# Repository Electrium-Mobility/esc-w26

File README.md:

# Electrium Mobility 2026 ESC
This repository contains all the firmware and hardware for Electrium Mobility's 2026 ESC, which is a 36V/15A 3-phase BLDC motor controller built around the STSPIN32G4 SiP's integrated gate driver and STM32G4 MCU, supporting 6-step and FOC commutation!

## Architecture

## Features

### Power
- **Voltage**: 10-36V (maximum 10S battery pack)
- **Current**: 15A continuous (25A peak)
- **Power**: 500W (implied by above)
- External 5V/1A Buck Regulator
- Internal VCC (using 10V)/200mA Buck Regulator
- Internal 3.3V/150mA LDO
- 1410uF Bulk Capacitor Bank (bleed resistor discharges it in 1 min)

### Input Protection
- Reverse Polarity Protection (dual back-to-back PMOS)
- Inrush Current Limiting (RC soft-start)
- Transient Overvoltage Protection (60V TVS clamp)
- Short-circuit and Overcurrent Protection (SCREF divider)

### Sensing
- Phase Currents (0.5m shunt resistors) using Internal PGA with Overcurrent Protection (note: measures negative currents, but regenerative braking is not supported)
- Phase Voltages (for sensorless feedback method using BEMF zero-crossings)
- PCB Temperature (NTC thermistor)

### Interfaces
- Power Supply Input (VM+, VM-)
- SWD Programming/Debug (STDC14)
- **Throttle**: UART (digital commands), ADC (analog pot)
- **Motor**: Phase Outputs (U, V, W), Hall Sensors (A, B, C), Winding Temperature
- CAN (FD)
- Expansion Headers: SPI, I2C, 4 unused pins

### User I/O
- **Buttons**: RESET, BOOT, USER
- **LEDs**: Power Rails, READY, FAULT, 2 configurable (STATUS1, STATUS2)
- Onboard Test Points

### Board 
- 4-layer (stackup: Signal/Power, Ground, Ground, Signal)
- 125x80mm with 2oz Outer and 0.5oz Inner Copper
- Partitioned Grounding Scheme (separates high-power PGND and logic GND)

## Schematic

## Routing

### Coloured (Traces Only, With Zones and Silkscreen)

### Colourless (Traces Only, With Zones and Silkscreen)

## 3D Renders

## Assembled Board
⚠️Under Construction⚠️

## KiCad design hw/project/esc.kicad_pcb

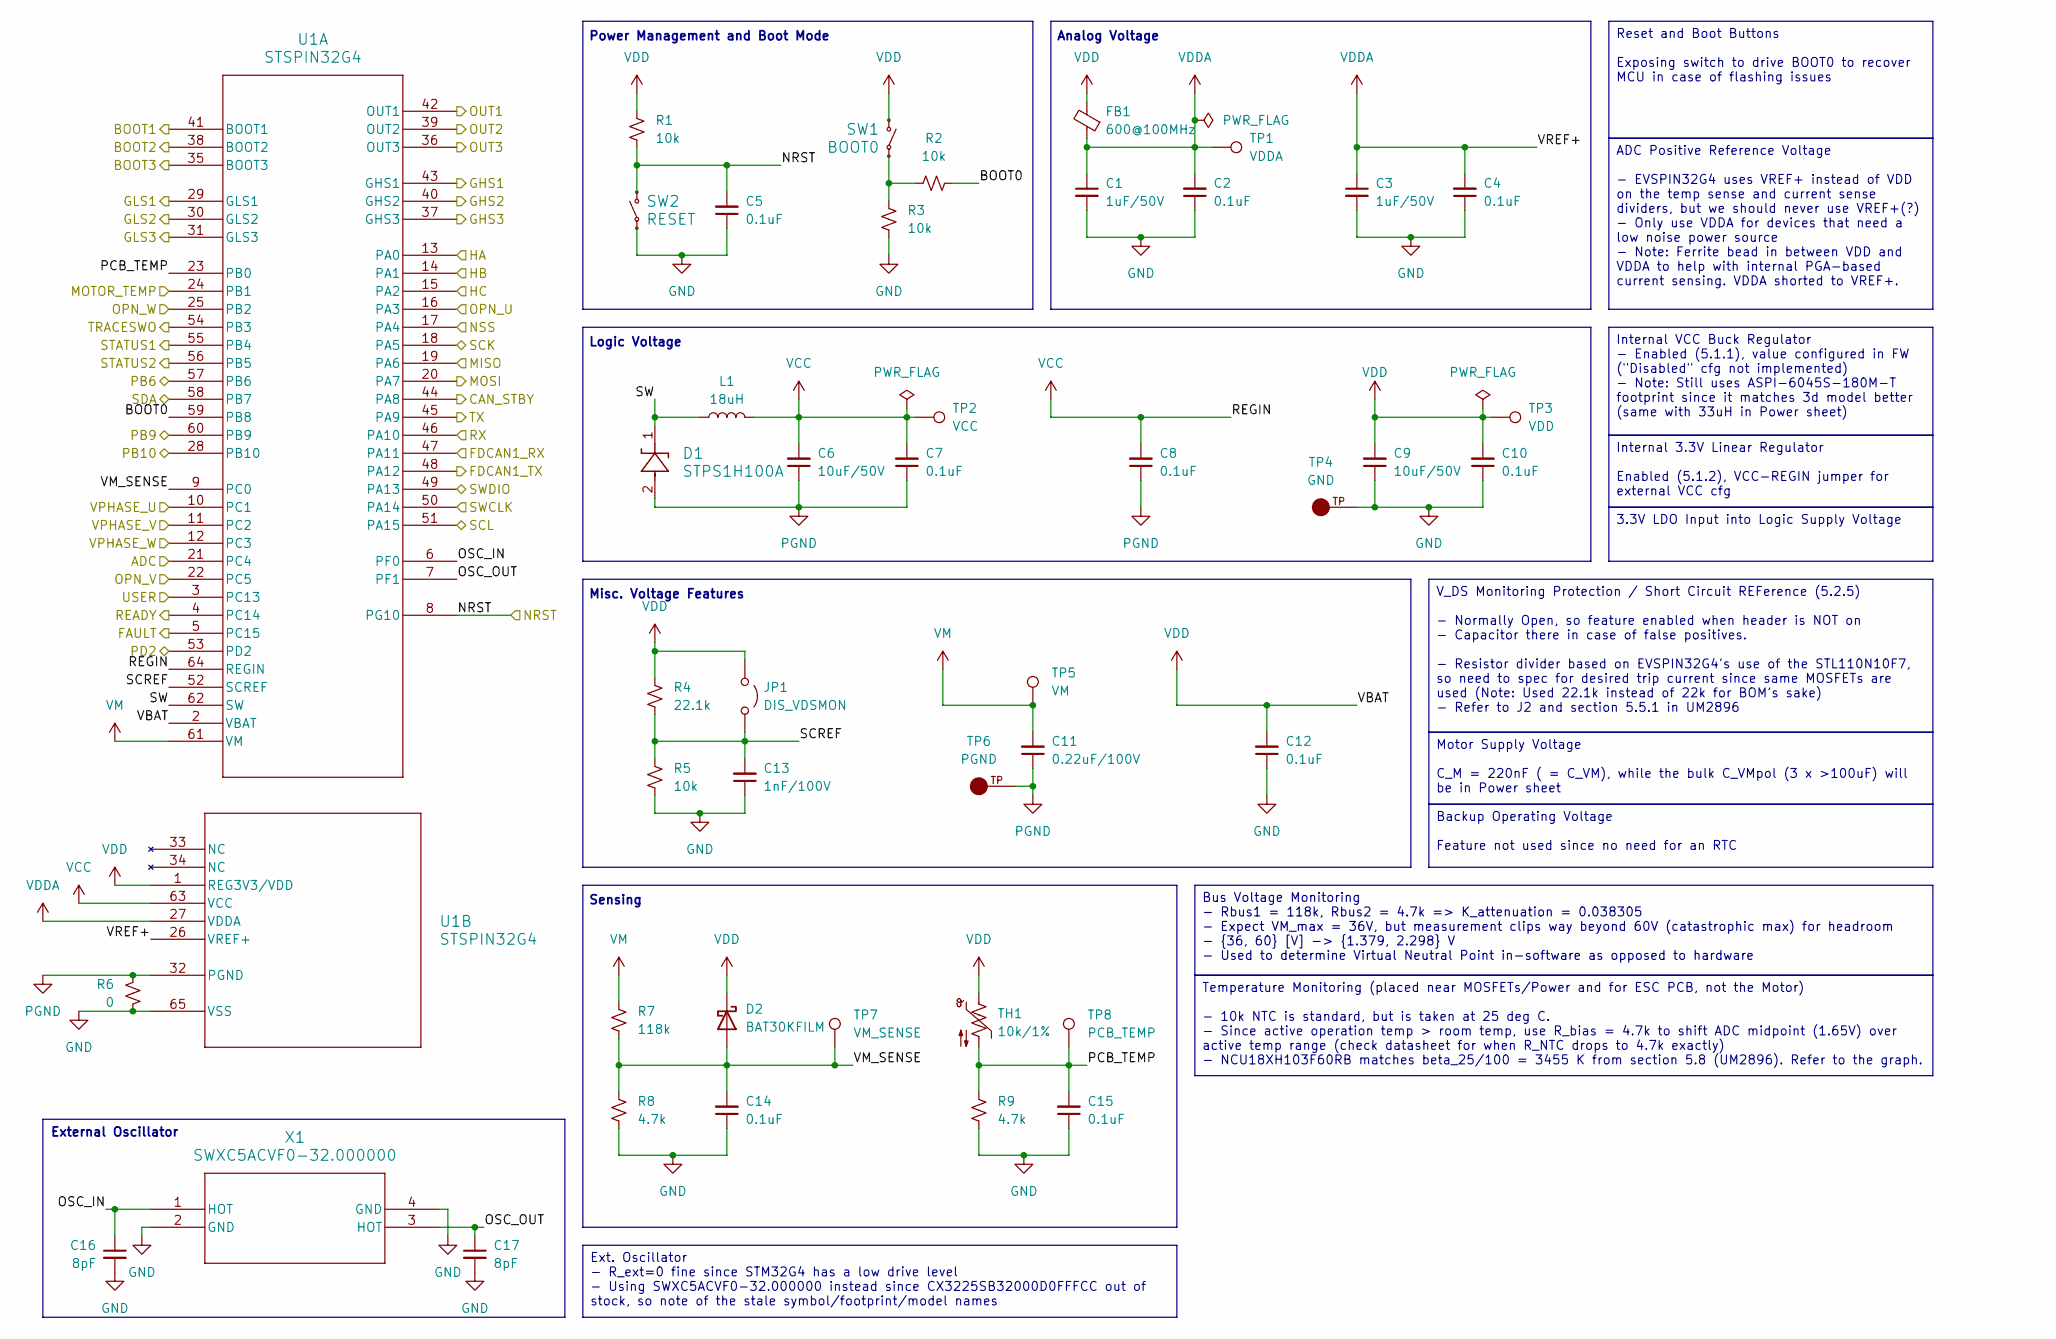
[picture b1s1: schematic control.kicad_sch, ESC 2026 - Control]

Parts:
C1, C3: 1uF/50V; C_0603_1608Metric; LCSC C15849
C2, C4, C5, C7, C8, C10, C12, C14, C15: 0.1uF; C_0603_1608Metric; LCSC C15725
C6, C9: 10uF/50V; C_0805_2012Metric; LCSC C440198
C11: 0.22uF/100V; C_0603_1608Metric; LCSC C2169715
C13: 1nF/100V; C_0603_1608Metric; LCSC C113793
C16, C17: 8pF; C_0603_1608Metric; LCSC C519117
D1: STPS1H100A; SMA_STM; LCSC C165701
D2: BAT30KFILM; D_SOD-523; LCSC C2926449
FB1: 600@100MHz; L_0603_1608Metric; LCSC C304319
JP1: DIS_VDSMON; PinHeader_1x02_P2.54mm_Vertical; LCSC C5426960
L1: 18uH; L_Sunlord_SWPA6045S; LCSC C96954
R1, R2, R3, R5: 10k; R_0603_1608Metric; LCSC C25804
R4: 22.1k; R_0603_1608Metric; LCSC C25961
R6: 0; R_0603_1608Metric; LCSC C21189
R7: 118k; R_0603_1608Metric; LCSC C25806
R8, R9: 4.7k; R_0603_1608Metric; LCSC C23162
SW1: BOOT0; TS-1187A-B-A-B; LCSC C318884
SW2: RESET; TS-1187A-B-A-B; LCSC C318884
TH1: 10k/1%; R_0603_1608Metric; LCSC C440252
TP1: VDDA; TestPoint_Pad_D1.0mm_with_More_Clearance
TP2: VCC; TestPoint_Pad_D1.0mm_with_More_Clearance
TP3: VDD; TestPoint_Pad_D1.0mm_with_More_Clearance
TP4: GND; KEYSTONE_5016; PARTREV D; DigiKey_Part_Number 36-5016CT-ND
TP5: VM; TestPoint_Pad_D1.0mm_with_More_Clearance
TP6: PGND; KEYSTONE_5016; PARTREV D; DigiKey_Part_Number 36-5016CT-ND
TP7: VM_SENSE; TestPoint_Pad_D1.0mm_with_More_Clearance
TP8: PCB_TEMP; TestPoint_Pad_D1.0mm_with_More_Clearance
U1: STSPIN32G4; QFN_IN32G4_STM; LCSC C7434864
X1: SWXC5ACVF0-32.000000; xtal4_CX3225SB_AVX; LCSC C22399832

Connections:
/Control/ADC: U1.21 (PC4); also elsewhere on the board
/Control/BOOT0: R2.2, U1.59 (PB8)
/Control/BOOT1: U1.41 (BOOT1); also elsewhere on the board
/Control/BOOT2: U1.38 (BOOT2); also elsewhere on the board
/Control/BOOT3: U1.35 (BOOT3); also elsewhere on the board
/Control/CAN_STBY: U1.44 (PA8); also elsewhere on the board
/Control/FAULT: U1.5 (PC15); also elsewhere on the board
/Control/FDCAN1_RX: U1.47 (PA11); also elsewhere on the board
/Control/FDCAN1_TX: U1.48 (PA12); also elsewhere on the board
/Control/GHS1: U1.43 (GHS1); also elsewhere on the board
/Control/GHS2: U1.40 (GHS2); also elsewhere on the board
/Control/GHS3: U1.37 (GHS3); also elsewhere on the board
/Control/GLS1: U1.29 (GLS1); also elsewhere on the board
/Control/GLS2: U1.30 (GLS2); also elsewhere on the board
/Control/GLS3: U1.31 (GLS3); also elsewhere on the board
/Control/HA: U1.13 (PA0); also elsewhere on the board
/Control/HB: U1.14 (PA1); also elsewhere on the board
/Control/HC: U1.15 (PA2); also elsewhere on the board
/Control/MISO: U1.19 (PA6); also elsewhere on the board
/Control/MOSI: U1.20 (PA7); also elsewhere on the board
/Control/MOTOR_TEMP: U1.24 (PB1); also elsewhere on the board
/Control/NRST: C5.2, R1.2, SW2.1, SW2.2, U1.8 (PG10); also elsewhere on the board
/Control/NSS: U1.17 (PA4); also elsewhere on the board
/Control/OPN_U: U1.16 (PA3); also elsewhere on the board
/Control/OPN_V: U1.22 (PC5); also elsewhere on the board
/Control/OPN_W: U1.25 (PB2); also elsewhere on the board
/Control/OSC_IN: C16.1, U1.6 (PF0), X1.1 (HOT)
/Control/OSC_OUT: C17.1, U1.7 (PF1), X1.3 (HOT)
/Control/PB6: U1.57 (PB6); also elsewhere on the board
/Control/PB9: U1.60 (PB9); also elsewhere on the board
/Control/PB10: U1.28 (PB10); also elsewhere on the board
/Control/PCB_TEMP: C15.2, R9.1, TH1.2, TP8.1 (1_1), U1.23 (PB0)
/Control/PD2: U1.53 (PD2); also elsewhere on the board
/Control/READY: U1.4 (PC14); also elsewhere on the board
/Control/RX: U1.46 (PA10); also elsewhere on the board
/Control/SCK: U1.18 (PA5); also elsewhere on the board
/Control/SCL: U1.51 (PA15); also elsewhere on the board
/Control/SCREF: C13.2, JP1.2 (B), R4.2, R5.1, U1.52 (SCREF)
/Control/SDA: U1.58 (PB7); also elsewhere on the board
/Control/STATUS1: U1.55 (PB4); also elsewhere on the board
/Control/STATUS2: U1.56 (PB5); also elsewhere on the board
/Control/SW: D1.1, L1.1, U1.62 (SW)
/Control/SWCLK: U1.50 (PA14); also elsewhere on the board
/Control/SWDIO: U1.49 (PA13); also elsewhere on the board
/Control/TRACESWO: U1.54 (PB3); also elsewhere on the board
/Control/TX: U1.45 (PA9); also elsewhere on the board
/Control/USER: U1.3 (PC13); also elsewhere on the board
/Control/VM_SENSE: C14.2, D2.2 (A), R7.2, R8.1, TP7.1 (1_1), U1.9 (PC0)
/Control/VPHASE_U: U1.10 (PC1); also elsewhere on the board
/Control/VPHASE_V: U1.11 (PC2); also elsewhere on the board
/Control/VPHASE_W: U1.12 (PC3); also elsewhere on the board
/Drive/U: U1.42 (OUT1); also elsewhere on the board
/Drive/V: U1.39 (OUT2); also elsewhere on the board
/Drive/W: U1.36 (OUT3); also elsewhere on the board
GND: C1.2, C2.1, C3.2, C4.1, C5.1, C9.1, C10.1, C12.1, C13.1, C14.1, C15.1, C16.2, C17.2, R3.2, R5.2, R6.1, R8.2, R9.2, SW2.3, SW2.4, TP4.TP, U1.65 (VSS), X1.2 (GND), X1.4 (GND); also elsewhere on the board
unnamed: R2.1, R3.1, SW1.3, SW1.4
PGND: C6.1, C7.1, C8.1, C11.1, D1.2, R6.2, TP6.TP, U1.32 (PGND); also elsewhere on the board
VCC: C6.2, C7.2, C8.2, L1.2, TP2.1 (1_1), U1.63 (VCC), U1.64 (REGIN); also elsewhere on the board
VDD: C9.2, C10.2, C12.2, D2.1 (K), FB1.2, JP1.1 (A), R1.1, R4.1, SW1.1, SW1.2, TH1.1, TP3.1 (1_1), U1.1 (REG3V3/VDD), U1.2 (VBAT); also elsewhere on the board
VDDA: C1.1, C2.2, C3.1, C4.2, FB1.1, TP1.1 (1_1), U1.26 (VREF+), U1.27 (VDDA)
VM: C11.2, R7.1, TP5.1 (1_1), U1.61 (VM); also elsewhere on the board

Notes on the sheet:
Analog Voltage
Misc. Voltage Features
Logic Voltage
Sensing
Power Management and Boot Mode
External Oscillator
Backup Operating Voltage Feature not used since no need for an RTC
3.3V LDO Input into Logic Supply Voltage
V_DS Monitoring Protection / Short Circuit REFerence (5.2.5) - Normally Open, so feature enabled when header is NOT on - Capacitor there in case of false positives. - Resistor divider based on EVSPIN32G4's use of the STL110N10F7, so need to spec for desired trip current since same MOSFETs are used 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
Internal 3.3V Linear Regulator Enabled (5.1.2), VCC-REGIN jumper for external VCC cfg
Internal VCC Buck Regulator - Enabled (5.1.1), value configured in FW ("Disabled" cfg not implemented) - Note: Still uses ASPI-6045S-180M-T footprint since it matches 3d model better (same with 33uH in Power sheet)
Temperature Monitoring (placed near MOSFETs/Power and for ESC PCB, not the Motor) - 10k NTC is standard, but is taken at 25 deg C. - Since active operation temp > room temp, use R_bias = 4.7k to shift ADC midpoint (1.65V) over active temp range (check datasheet for when R_NTC drops to 4.7k exactly)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
ADC Positive Reference Voltage - EVSPIN32G4 uses VREF+ instead of VDD on the temp sense and current sense dividers, but we should never use VREF+(?) - Only use VDDA for devices that need a low noise power source - Note: Ferrite bead in between VDD and VDDA to help with internal PGA-based current se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
Ext. Oscillator - R_ext=0 fine since STM32G4 has a low drive level - Using SWXC5ACVF0-32.000000 instead since CX3225SB32000D0FFFCC out of stock, so note of the stale symbol/footprint/model names
Motor Supply Voltage C_M = 220nF ( = C_VM), while the bulk C_VMpol (3 x >100uF) will be in Power sheet
Reset and Boot Buttons Exposing switch to drive BOOT0 to recover MCU in case of flashing issues
Bus Voltage Monitoring - Rbus1 = 118k, Rbus2 = 4.7k => K_attenuation = 0.038305 - Expect VM_max = 36V, but measurement clips way beyond 60V (catastrophic max) for headroom - {36, 60} [V] -> {1.379, 2.298} V - Used to determine Virtual Neutral Point in-software as opposed to hardware

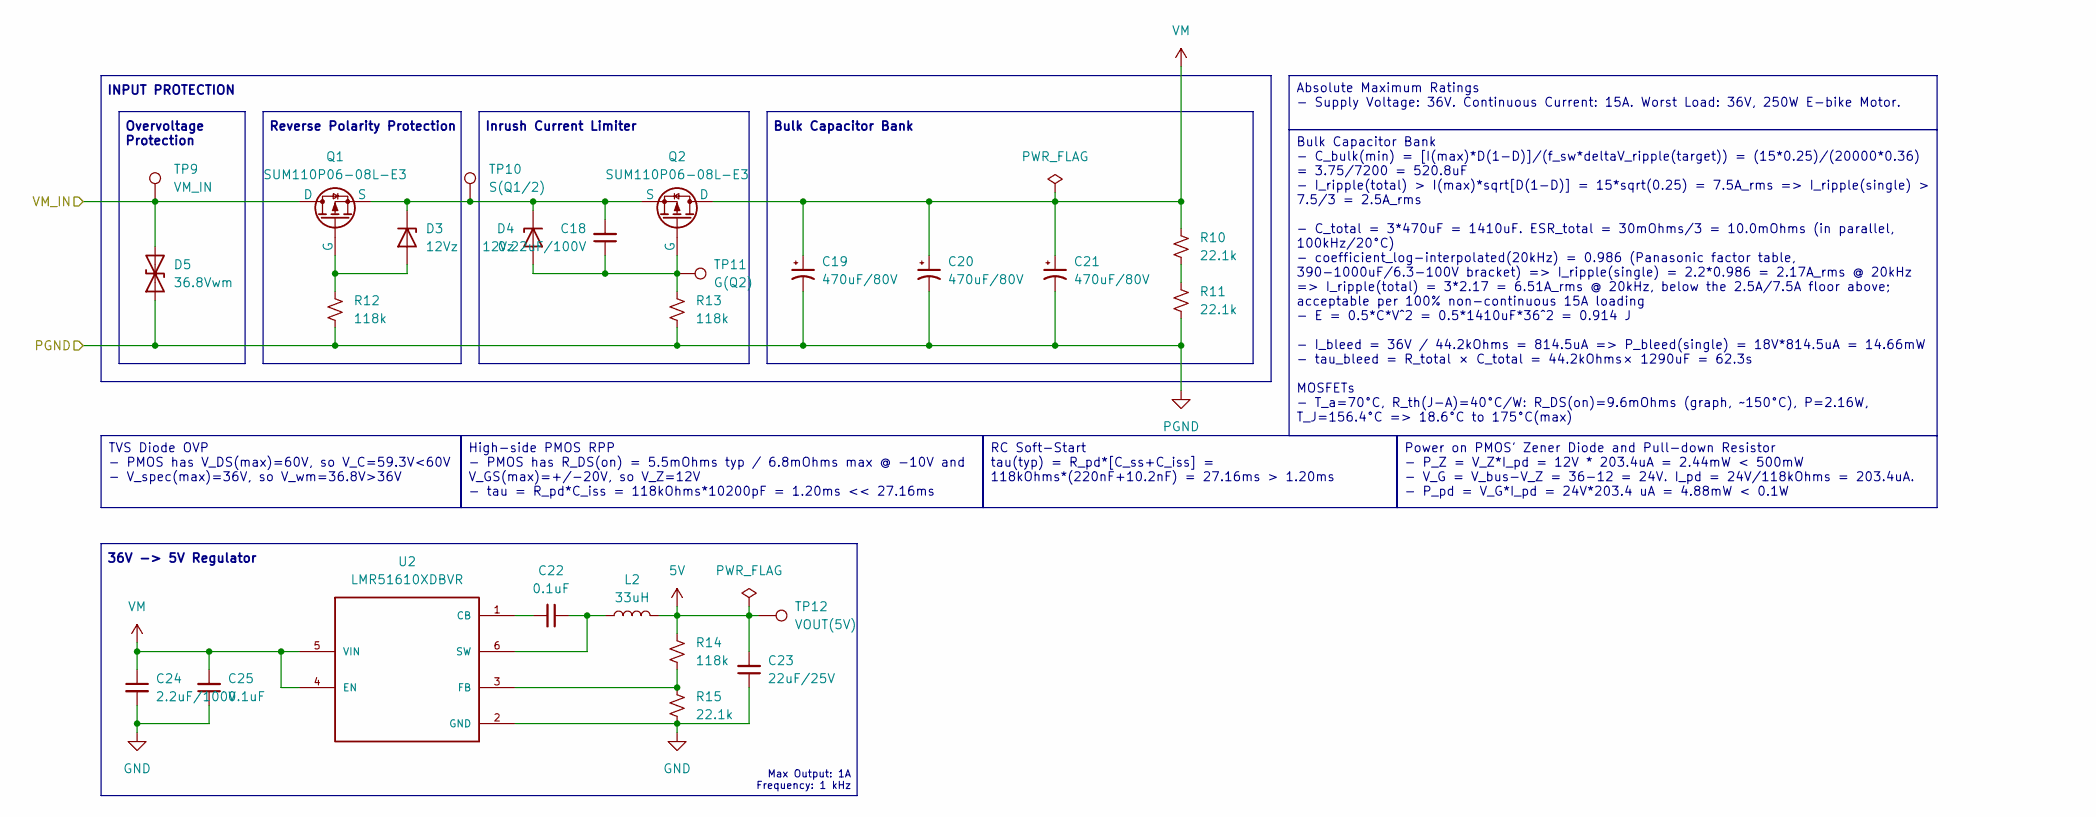
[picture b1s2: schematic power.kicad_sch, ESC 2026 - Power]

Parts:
C18: 0.22uF/100V; C_0603_1608Metric; LCSC C2169715
C19, C20, C21: 470uF/80V; CP_Radial_D12.5mm_P5.00mm; LCSC C385881
C22, C25: 0.1uF; C_0603_1608Metric; LCSC C15725
C23: 22uF/25V; C_0805_2012Metric; LCSC C45783
C24: 2.2uF/100V; C_0805_2012Metric; LCSC C2981733
D3, D4: 12Vz; D_SOD-123; LCSC C699126
D5: 36.8Vwm; D_SMB; LCSC C468909
L2: 33uH; L_Sunlord_SWPA6045S; LCSC C83451
Q1, Q2: SUM110P06-08L-E3; TO-263-2; LCSC C5364638
R10, R11, R15: 22.1k; R_0603_1608Metric; LCSC C25961
R12, R13, R14: 118k; R_0603_1608Metric; LCSC C25806
TP9: VM_IN; TestPoint_Pad_D1.0mm_with_More_Clearance
TP10: S(Q1/2); TestPoint_Pad_D1.0mm_with_More_Clearance
TP11: G(Q2); TestPoint_Pad_D1.0mm_with_More_Clearance
TP12: VOUT(5V); TestPoint_Pad_D1.0mm_with_More_Clearance
U2: LMR51610XDBVR; LMR51610XDBVR-SOT95P280X145-6N; PARTREV B; LCSC C20539658

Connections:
5V: C23.2, L2.2, R14.1, TP12.1 (1_1); also elsewhere on the board
/Peripherals/VM_IN: D5.2 (A2), Q1.2 (D), TP9.1 (1_1); also elsewhere on the board
GND: C23.1, C24.2, C25.1, R15.2, U2.2 (GND); also elsewhere on the board
unnamed: D3.2 (A), Q1.1 (G), R12.1
unnamed: C18.2, D3.1 (K), D4.1 (K), Q1.3 (S), Q2.3 (S), TP10.1 (1_1)
unnamed: C18.1, D4.2 (A), Q2.1 (G), R13.1, TP11.1 (1_1)
unnamed: R10.2, R11.1
unnamed: C22.2, U2.1 (CB)
unnamed: R14.2, R15.1, U2.3 (FB)
unnamed: C22.1, L2.1, U2.6 (SW)
PGND: C19.2, C20.2, C21.2, D5.1 (A1), R11.2, R12.2, R13.2; also elsewhere on the board
VM: C19.1, C20.1, C21.1, C24.1, C25.2, Q2.2 (D), R10.1, U2.4 (EN), U2.5 (VIN); also elsewhere on the board

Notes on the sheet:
Overvoltage Protection
Max Output: 1A Frequency: 1 kHz
36V -> 5V Regulator
INPUT PROTECTION
Inrush Current Limiter
Bulk Capacitor Bank
Reverse Polarity Protection
RC Soft-Start tau(typ) = R_pd*[C_ss+C_iss] = 118kOhms*(220nF+10.2nF) = 27.16ms > 1.20ms
TVS Diode OVP - PMOS has V_DS(max)=60V, so V_C=59.3V<60V - V_spec(max)=36V, so V_wm=36.8V>36V
High-side PMOS RPP - PMOS has R_DS(on) = 5.5mOhms typ / 6.8mOhms max @ -10V and V_GS(max)=+/-20V, so V_Z=12V - tau = R_pd*C_iss = 118kOhms*10200pF = 1.20ms << 27.16ms
Power on PMOS' Zener Diode and Pull-down Resistor - P_Z = V_Z*I_pd = 12V * 203.4uA = 2.44mW < 500mW - V_G = V_bus−V_Z = 36−12 = 24V. I_pd = 24V/118kOhms = 203.4uA. - P_pd = V_G*I_pd = 24V*203.4 uA = 4.88mW < 0.1W
Absolute Maximum Ratings - Supply Voltage: 36V. Continuous Current: 15A. Worst Load: 36V, 250W E-bike Motor.
Bulk Capacitor Bank - C_bulk(min) = [I(max)*D(1−D)]/(f_sw*deltaV_ripple(target)) = (15*0.25)/(20000*0.36) = 3.75/7200 = 520.8uF - I_ripple(total) > I(max)*sqrt[D(1−D)] = 15*sqrt(0.25) = 7.5A_rms => I_ripple(single) > 7.5/3 = 2.5A_rms - C_total = 3*470uF = 1410uF. ESR_total = 30mOhms/3 = 10.0mOhms (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

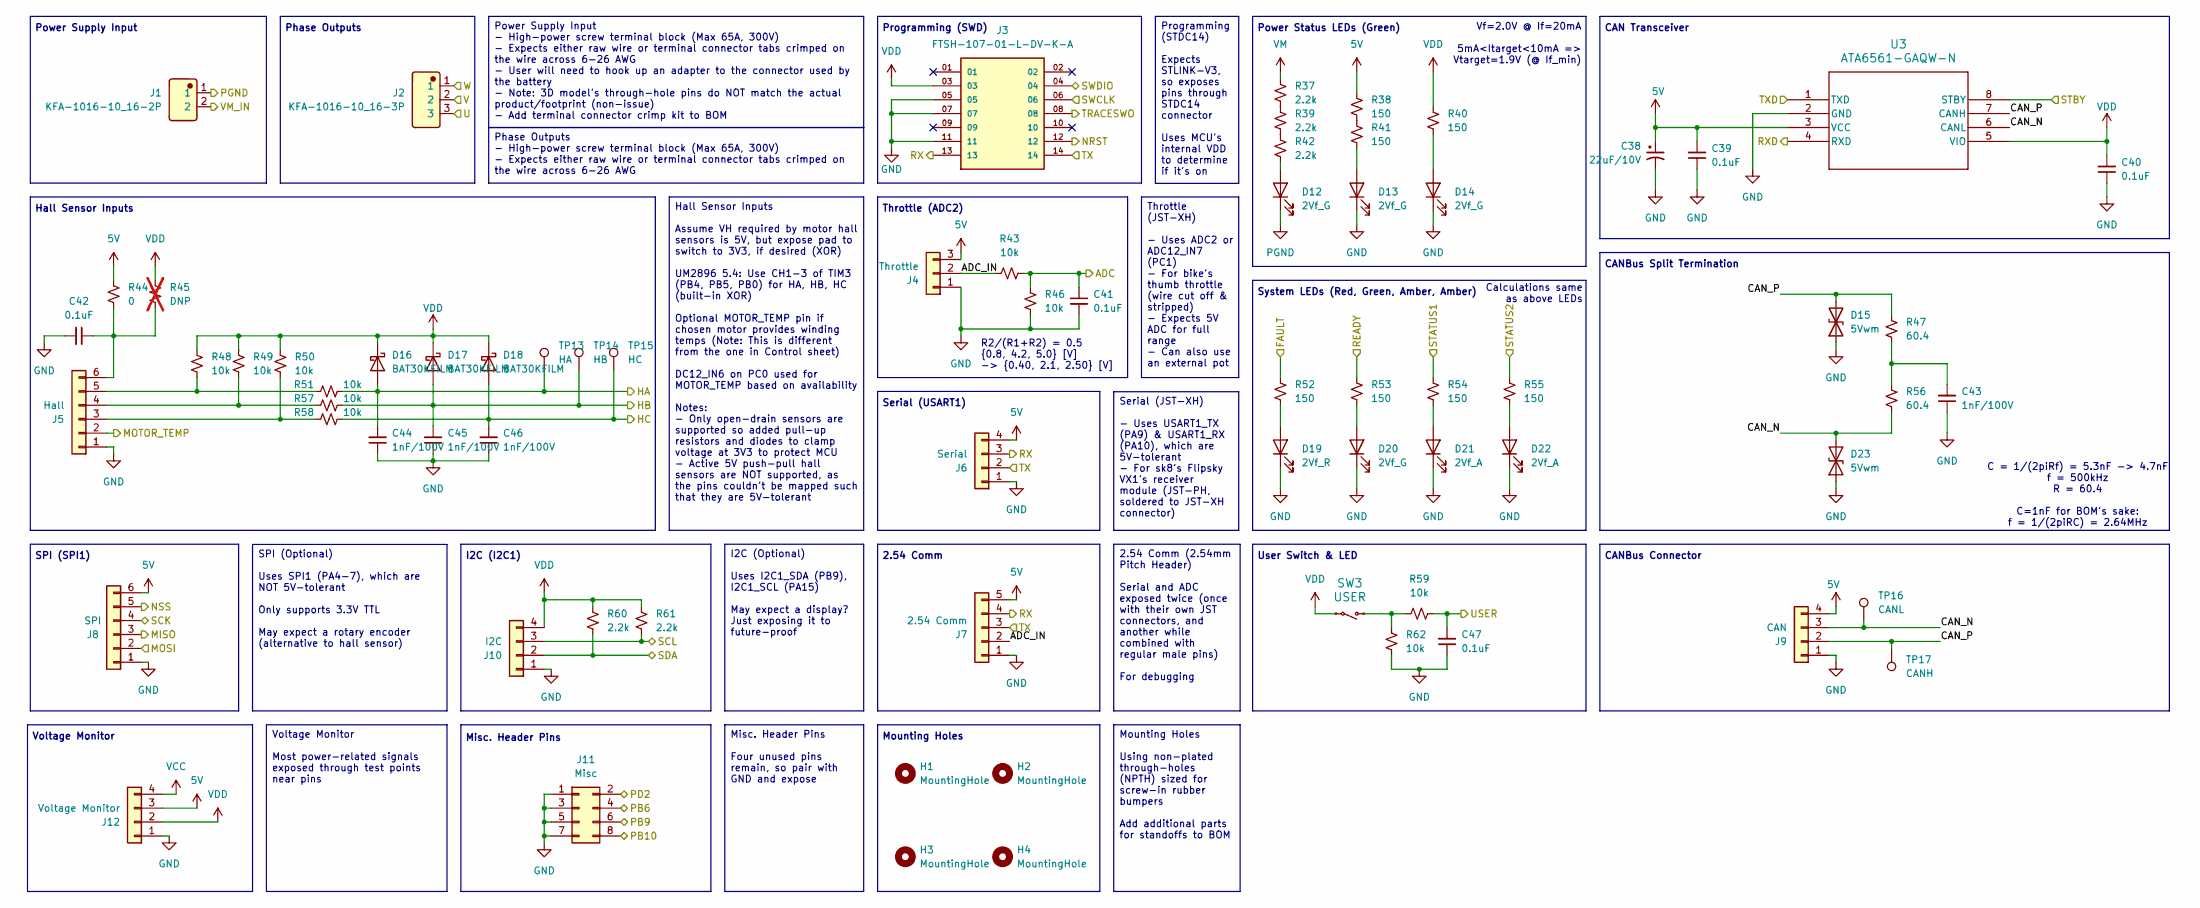
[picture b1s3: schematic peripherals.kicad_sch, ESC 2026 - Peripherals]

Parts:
C38: 22uF/10V; EEEFKC220UAR; LCSC C401733
C39, C40, C41, C42, C47: 0.1uF; C_0603_1608Metric; LCSC C15725
C43, C44, C45, C46: 1nF/100V; C_0603_1608Metric; LCSC C113793
D12, D13, D14, D20: 2Vf_G; LED_0603_1608Metric; LCSC C125098
D15, D23: 5Vwm; D_SOD-523; LCSC C51912417
D16, D17, D18: BAT30KFILM; D_SOD-523; LCSC C2926449
D19: 2Vf_R; LED_0603_1608Metric; LCSC C94869
D21, D22: 2Vf_A; LED_0603_1608Metric; LCSC C5730905
H1, H2, H3, H4: MountingHole; MountingHole_3.2mm_M3
J1: KFA-1016-10_16-2P; Manufacturer Part KFA-1016-10.16-2P; LCSC C475110
J2: KFA-1016-10_16-3P; Manufacturer Part KFA-1016-10.16-3P; LCSC C475111
J3: FTSH-107-01-L-DV-K-A; SAMTEC_FTSH-107-01-L-DV-K-A; PARTREV H; DigiKey_Part_Number FTSH-107-01-L-DV-K-A-ND
J4: Throttle; JST_XH_B3B-XH-A_1x03_P2.50mm_Vertical; LCSC C144394
J5: Hall; JST_XH_B6B-XH-A_1x06_P2.50mm_Vertical; LCSC C144397
J6: Serial; JST_XH_B4B-XH-A_1x04_P2.50mm_Vertical; LCSC C144395
J7: 2.54 Comm; PinHeader_1x05_P2.54mm_Vertical; LCSC C3347212
J8: SPI; PinHeader_1x06_P2.54mm_Vertical; LCSC C5427040
J9: CAN; JST_XH_B4B-XH-A_1x04_P2.50mm_Vertical; LCSC C144395
J10: I2C; PinHeader_1x04_P2.54mm_Vertical; LCSC C3329732
J11: Misc; PinHeader_2x04_P2.54mm_Vertical; LCSC C3333874
J12: Voltage Monitor; PinHeader_1x04_P2.54mm_Vertical; LCSC C3329732
R37, R39, R42, R60, R61: 2.2k; R_0603_1608Metric; LCSC C4190
R38, R40, R41, R52, R53, R54, R55: 150; R_0603_1608Metric; LCSC C22808
R43, R46, R48, R49, R50, R51, R57, R58, R59, R62: 10k; R_0603_1608Metric; LCSC C25804
R44: 0; R_0603_1608Metric; LCSC C21189
R45: DNP; R_0603_1608Metric; not fitted
R47, R56: 60.4; R_0603_1608Metric; LCSC C23090
SW3: USER; TS-1187A-B-A-B; LCSC C318884
TP13: HA; TestPoint_Pad_D1.0mm_with_More_Clearance
TP14: HB; TestPoint_Pad_D1.0mm_with_More_Clearance
TP15: HC; TestPoint_Pad_D1.0mm_with_More_Clearance
TP16: CANL; TestPoint_Pad_D1.0mm_with_More_Clearance
TP17: CANH; TestPoint_Pad_D1.0mm_with_More_Clearance
U3: ATA6561-GAQW-N; SOIC8_4P9X3P9MC_MCH; LCSC C616016

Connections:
5V: C38.1, C39.2, J4.3, J6.4, J7.5, J8.6, J9.4, J12.3, R38.1, R44.1, U3.3 (VCC); also elsewhere on the board
/Control/ADC: C41.1, R43.2, R46.2; also elsewhere on the board
/Control/CAN_STBY: U3.8 (STBY); also elsewhere on the board
/Control/FAULT: R52.1; also elsewhere on the board
/Control/FDCAN1_RX: U3.4 (RXD); also elsewhere on the board
/Control/FDCAN1_TX: U3.1 (TXD); also elsewhere on the board
/Control/HA: C44.2, D16.2 (A), R51.2, TP13.1 (1_1); also elsewhere on the board
/Control/HB: C45.2, D17.2 (A), R57.2, TP14.1 (1_1); also elsewhere on the board
/Control/HC: C46.2, D18.2 (A), R58.2, TP15.1 (1_1); also elsewhere on the board
/Control/MISO: J8.3; also elsewhere on the board
/Control/MOSI: J8.2; also elsewhere on the board
/Control/MOTOR_TEMP: J5.2; also elsewhere on the board
/Control/NRST: J3.12; also elsewhere on the board
/Control/NSS: J8.5; also elsewhere on the board
/Control/PB6: J11.4; also elsewhere on the board
/Control/PB9: J11.6; also elsewhere on the board
/Control/PB10: J11.8; also elsewhere on the board
/Control/PD2: J11.2; also elsewhere on the board
/Control/READY: R53.1; also elsewhere on the board
/Control/RX: J3.13, J6.3, J7.4; also elsewhere on the board
/Control/SCK: J8.4; also elsewhere on the board
/Control/SCL: J10.3, R61.1; also elsewhere on the board
/Control/SDA: J10.2, R60.1; also elsewhere on the board
/Control/STATUS1: R54.1; also elsewhere on the board
/Control/STATUS2: R55.1; also elsewhere on the board
/Control/SWCLK: J3.06; also elsewhere on the board
/Control/SWDIO: J3.04; also elsewhere on the board
/Control/TRACESWO: J3.08; also elsewhere on the board
/Control/TX: J3.14, J6.2, J7.3; also elsewhere on the board
/Control/USER: C47.2, R59.2; also elsewhere on the board
/Drive/U: J2.3; also elsewhere on the board
/Drive/V: J2.2; also elsewhere on the board
/Drive/W: J2.1; also elsewhere on the board
/Peripherals/ADC_IN: J4.2, J7.2, R43.1
/Peripherals/CAN_N: D23.2 (A2), J9.3, R56.2, TP16.1 (1_1), U3.6 (CANL)
/Peripherals/CAN_P: D15.2 (A2), J9.2, R47.1, TP17.1 (1_1), U3.7 (CANH)
/Peripherals/VM_IN: J1.2; also elsewhere on the board
GND: C38.2, C39.1, C40.1, C41.2, C42.2, C43.1, C44.1, C45.1, C46.1, C47.1, D13.1 (K), D14.1 (K), D15.1 (A1), D19.1 (K), D20.1 (K), D21.1 (K), D22.1 (K), D23.1 (A1), J3.05, J3.07, J3.11, J4.1, J5.1, J6.1, J7.1, J8.1, J9.1, J10.1, J11.1, J11.3, J11.5, J11.7, J12.1, R46.1, R62.2, U3.2 (GND); also elsewhere on the board
unnamed: C43.2, R47.2, R56.1
unnamed: D12.2 (A), R42.1
unnamed: D13.2 (A), R41.2
unnamed: D14.2 (A), R40.2
unnamed: D19.2 (A), R52.2
unnamed: D20.2 (A), R53.2
unnamed: D21.2 (A), R54.2
unnamed: D22.2 (A), R55.2
unnamed: J5.3, R50.2, R58.1
unnamed: J5.4, R49.2, R57.1
unnamed: J5.5, R48.2, R51.1
unnamed: C42.1, J5.6, R44.2, R45.2
unnamed: R37.1, R39.2
unnamed: R38.2, R41.1
unnamed: R39.1, R42.2
unnamed: R59.1, R62.1, SW3.1, SW3.2
PGND: D12.1 (K), J1.1; also elsewhere on the board
VCC: J12.4; also elsewhere on the board
VDD: C40.2, D16.1 (K), D17.1 (K), D18.1 (K), J3.03, J10.4, J12.2, R40.1, R45.1, R48.1, R49.1, R50.1, R60.2, R61.2, SW3.3, SW3.4, U3.5 (VIO); also elsewhere on the board
VM: R37.2; also elsewhere on the board

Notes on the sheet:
Vf=2.0V @ If=20mA 5mA<Itarget<10mA => Vtarget=1.9V (@ If_min)
CANBus Connector
C = 1/(2piRf) = 5.3nF -> 4.7nF f = 500kHz R = 60.4 C=1nF for BOM's sake: f = 1/(2piRC) = 2.64MHz
Power Supply Input
Mounting Holes
CANBus Split Termination
Programming (SWD)
CAN Transceiver
SPI (SPI1)
Misc. Header Pins
System LEDs (Red, Green, Amber, Amber)
Hall Sensor Inputs
R2/(R1+R2) = 0.5 {0.8, 4.2, 5.0} [V] -> {0.40, 2.1, 2.50} [V]
Calculations same as above LEDs
I2C (I2C1)
Serial (USART1)
2.54 Comm
Voltage Monitor
Power Status LEDs (Green)
Phase Outputs
User Switch & LED
Throttle (ADC2)
Hall Sensor Inputs Assume VH required by motor hall sensors is 5V, but expose pad to switch to 3V3, if desired (XOR) UM2896 5.4: Use CH1-3 of TIM3 (PB4, PB5, PB0) for HA, HB, HC (built-in XOR) Optional MOTOR_TEMP pin if chosen motor provides winding temps (Note: This is different from the one in Co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
Misc. Header Pins Four unused pins remain, so pair with GND and expose
Serial (JST-XH) - Uses USART1_TX (PA9) & USART1_RX (PA10), which are 5V-tolerant - For sk8's Flipsky VX1's receiver module (JST-PH, soldered to JST-XH connector)
Voltage Monitor Most power-related signals exposed through test points near pins
Programming (STDC14) Expects STLINK-V3, so exposes pins through STDC14 connector Uses MCU's internal VDD to determine if it's on
2.54 Comm (2.54mm Pitch Header) Serial and ADC exposed twice (once with their own JST connectors, and another while combined with regular male pins) For debugging
Phase Outputs - High-power screw terminal block (Max 65A, 300V) - Expects either raw wire or terminal connector tabs crimped on the wire across 6-26 AWG
I2C (Optional) Uses I2C1_SDA (PB9), I2C1_SCL (PA15) May expect a display? Just exposing it to future-proof
Throttle (JST-XH) - Uses ADC2 or ADC12_IN7 (PC1) - For bike's thumb throttle (wire cut off & stripped) - Expects 5V ADC for full range - Can also use an external pot
Power Supply Input - High-power screw terminal block (Max 65A, 300V) - Expects either raw wire or terminal connector tabs crimped on the wire across 6-26 AWG - User will need to hook up an adapter to the connector used by the battery - Note: 3D model's through-hole pins do NOT match the actual prod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
SPI (Optional) Uses SPI1 (PA4-7), which are NOT 5V-tolerant Only supports 3.3V TTL May expect a rotary encoder (alternative to hall sensor)
Mounting Holes Using non-plated through-holes (NPTH) sized for screw-in rubber bumpers Add additional parts for standoffs to BOM

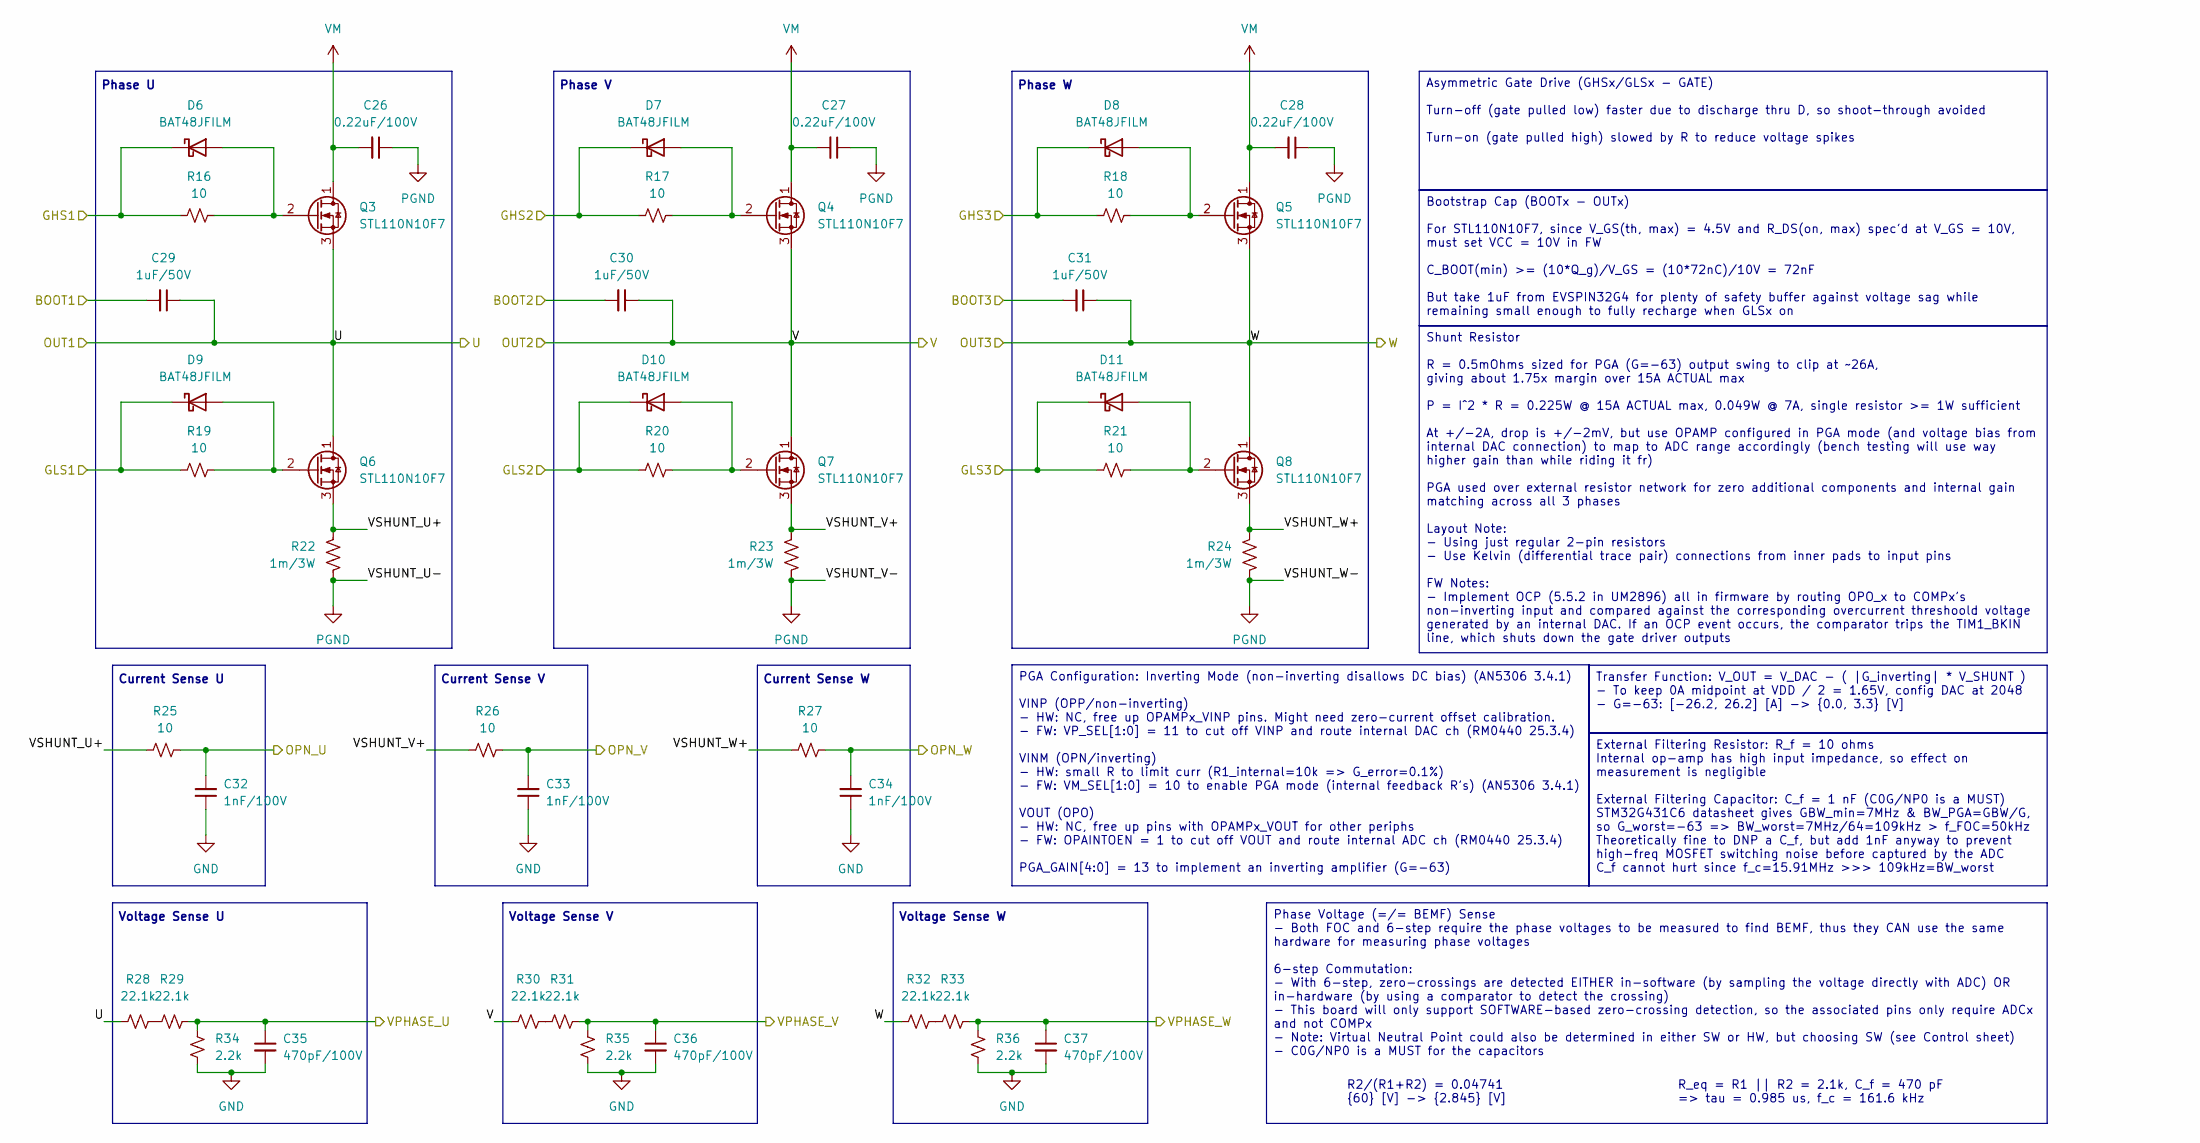
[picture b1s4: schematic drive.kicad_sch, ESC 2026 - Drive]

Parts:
C26, C27, C28: 0.22uF/100V; C_0603_1608Metric; LCSC C2169715
C29, C30, C31: 1uF/50V; C_0603_1608Metric; LCSC C15849
C32, C33, C34: 1nF/100V; C_0603_1608Metric; LCSC C113793
C35, C36, C37: 470pF/100V; C_0603_1608Metric; LCSC C326973
D6, D7, D8, D9, D10, D11: BAT48JFILM; D_SOD-323; LCSC C2798199
Q3, Q4, Q5, Q6, Q7, Q8: STL110N10F7; MOSFET_10N10F7_STM; LCSC C672185
R16, R17, R18, R19, R20, R21, R25, R26, R27: 10; R_0603_1608Metric; LCSC C22859
R22, R23, R24: 1m/3W; R_2512_6332Metric; LCSC C53280154
R28, R29, R30, R31, R32, R33: 22.1k; R_0603_1608Metric; LCSC C25961
R34, R35, R36: 2.2k; R_0603_1608Metric; LCSC C4190

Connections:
/Control/BOOT1: C29.2; also elsewhere on the board
/Control/BOOT2: C30.2; also elsewhere on the board
/Control/BOOT3: C31.2; also elsewhere on the board
/Control/GHS1: D6.1 (K), R16.1; also elsewhere on the board
/Control/GHS2: D7.1 (K), R17.1; also elsewhere on the board
/Control/GHS3: D8.1 (K), R18.1; also elsewhere on the board
/Control/GLS1: D9.1 (K), R19.1; also elsewhere on the board
/Control/GLS2: D10.1 (K), R20.1; also elsewhere on the board
/Control/GLS3: D11.1 (K), R21.1; also elsewhere on the board
/Control/OPN_U: C32.2, R25.2; also elsewhere on the board
/Control/OPN_V: C33.2, R26.2; also elsewhere on the board
/Control/OPN_W: C34.2, R27.2; also elsewhere on the board
/Control/VPHASE_U: C35.1, R29.2, R34.2; also elsewhere on the board
/Control/VPHASE_V: C36.1, R31.2, R35.2; also elsewhere on the board
/Control/VPHASE_W: C37.1, R33.2, R36.2; also elsewhere on the board
/Drive/U: C29.1, Q3.3 (S), Q6.1 (D), R28.1; also elsewhere on the board
/Drive/V: C30.1, Q4.3 (S), Q7.1 (D), R30.1; also elsewhere on the board
/Drive/VSHUNT_U+: Q6.3 (S), R22.1, R25.1
/Drive/VSHUNT_V+: Q7.3 (S), R23.1, R26.1
/Drive/VSHUNT_W+: Q8.3 (S), R24.1, R27.1
/Drive/W: C31.1, Q5.3 (S), Q8.1 (D), R32.1; also elsewhere on the board
GND: C32.1, C33.1, C34.1, C35.2, C36.2, C37.2, R34.1, R35.1, R36.1; also elsewhere on the board
unnamed: D6.2 (A), Q3.2 (G), R16.2
unnamed: D7.2 (A), Q4.2 (G), R17.2
unnamed: D8.2 (A), Q5.2 (G), R18.2
unnamed: D9.2 (A), Q6.2 (G), R19.2
unnamed: D10.2 (A), Q7.2 (G), R20.2
unnamed: D11.2 (A), Q8.2 (G), R21.2
unnamed: R28.2, R29.1
unnamed: R30.2, R31.1
unnamed: R32.2, R33.1
PGND: C26.1, C27.1, C28.1, R22.2, R23.2, R24.2; also elsewhere on the board
VM: C26.2, C27.2, C28.2, Q3.1 (D), Q4.1 (D), Q5.1 (D); also elsewhere on the board

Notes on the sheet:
Phase V
Voltage Sense V
Voltage Sense U
R2/(R1+R2) = 0.04741 {60} [V] -> {2.845} [V]
Voltage Sense W
Phase U
R_eq = R1 || R2 = 2.1k, C_f = 470 pF => tau = 0.985 us, f_c = 161.6 kHz
Current Sense V
Phase W
Current Sense W
Current Sense U
Bootstrap Cap (BOOTx - OUTx) For STL110N10F7, since V_GS(th, max) = 4.5V and R_DS(on, max) spec'd at V_GS = 10V, must set VCC = 10V in FW C_BOOT(min) >= (10*Q_g)/V_GS = (10*72nC)/10V = 72nF But take 1uF from EVSPIN32G4 for plenty of safety buffer against voltage sag while remaining small enough to 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
Phase Voltage (=/= BEMF) Sense - Both FOC and 6-step require the phase voltages to be measured to find BEMF, thus they CAN use the same hardware for measuring phase voltages 6-step Commutation: - With 6-step, zero-crossings are detected EITHER in-software (by sampling the voltage directly with ADC)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
PGA Configuration: Inverting Mode (non-inverting disallows DC bias) (AN5306 3.4.1) VINP (OPP/non-inverting) - HW: NC, free up OPAMPx_VINP pins. Might need zero-current offset calibration. - FW: VP_SEL[1:0] = 11 to cut off VINP and route internal DAC ch (RM0440 25.3.4) VINM (OPN/inverting) - HW: sma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
Transfer Function: V_OUT = V_DAC - ( |G_inverting| * V_SHUNT ) - To keep 0A midpoint at VDD / 2 = 1.65V, config DAC at 2048 - G=-63: [-26.2, 26.2] [A] -> {0.0, 3.3} [V]
Asymmetric Gate Drive (GHSx/GLSx - GATE) Turn-off (gate pulled low) faster due to discharge thru D, so shoot-through avoided Turn-on (gate pulled high) slowed by R to reduce voltage spikes
External Filtering Resistor: R_f = 10 ohms Internal op-amp has high input impedance, so effect on measurement is negligible External Filtering Capacitor: C_f = 1 nF (C0G/NP0 is a MUST) STM32G431C6 datasheet gives GBW_min=7MHz & BW_PGA=GBW/G, so G_worst=-63 => BW_worst=7MHz/64=109kHz > f_FOC=50kHz T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
Shunt Resistor R = 0.5mOhms sized for PGA (G=-63) output swing to clip at ~26A, giving about 1.75x margin over 15A ACTUAL max P = I^2 * R = 0.225W @ 15A ACTUAL max, 0.049W @ 7A, single resistor >= 1W sufficient At +/-2A, drop is +/-2mV, but use OPAMP configured in PGA mode (and voltage bias from in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
